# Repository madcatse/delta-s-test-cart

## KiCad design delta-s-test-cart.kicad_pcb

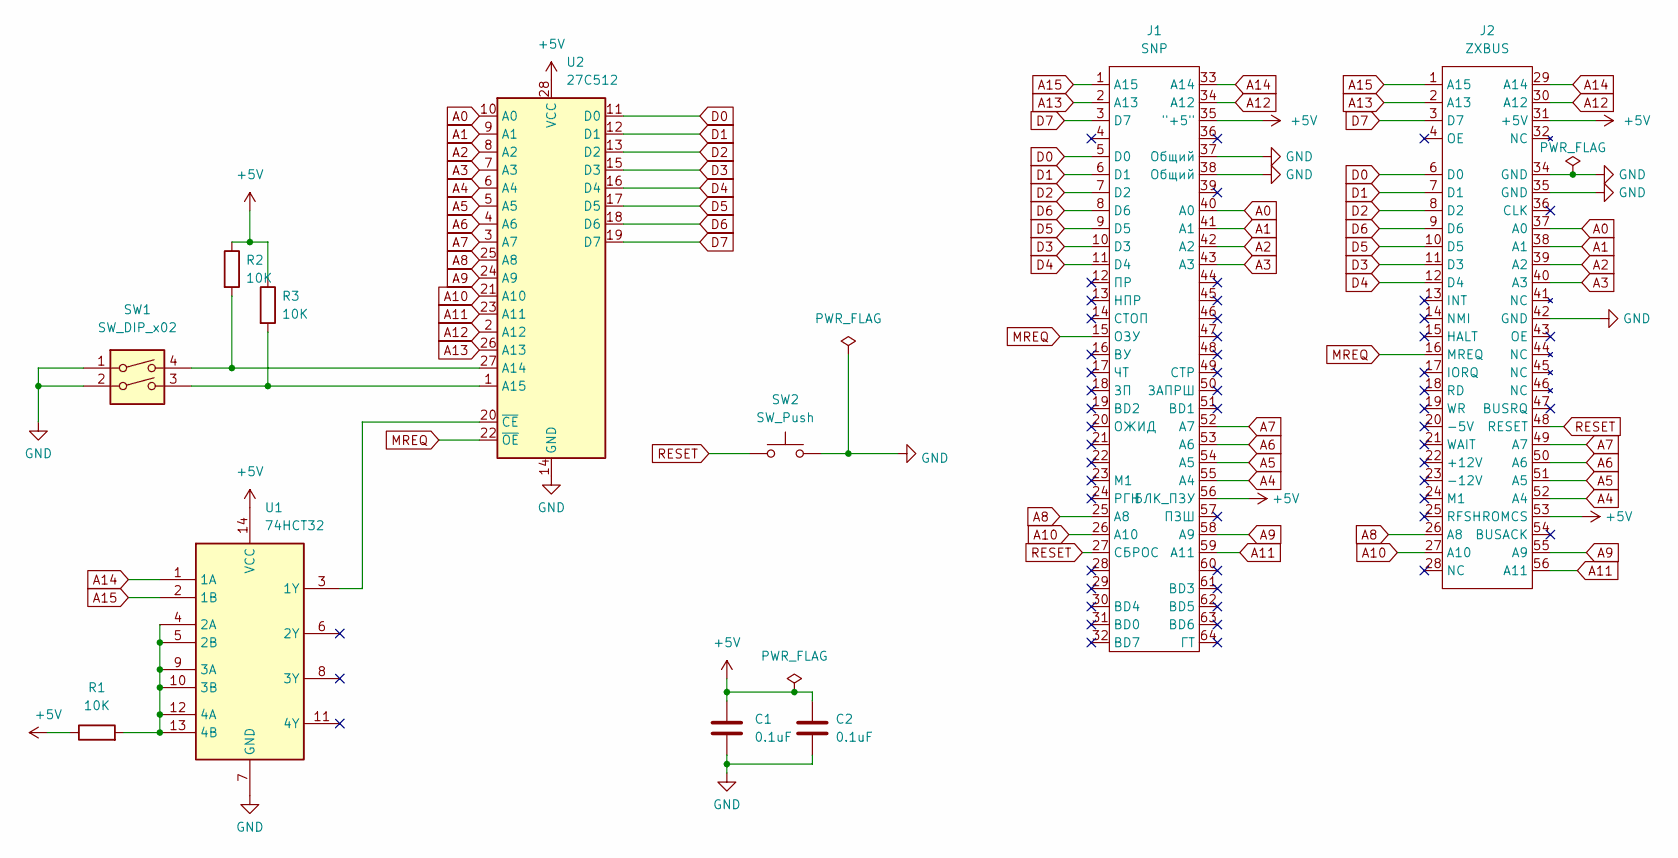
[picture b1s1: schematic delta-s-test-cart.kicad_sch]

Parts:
C1, C2: 0.1uF; C_Disc_D4.7mm_W2.5mm_P5.00mm
J1: SNP; SNP96
J2: ZXBUS; ZX SPECTRUM EDGE CONNECTOR (HORIZONTAL)
R1, R2, R3: 10K; R_Axial_DIN0207_L6.3mm_D2.5mm_P10.16mm_Horizontal
SW1: SW_DIP_x02; SW_DIP_SPSTx02_Slide_6.7x6.64mm_W7.62mm_P2.54mm_LowProfile
SW2: SW_Push; SW_PUSH_6mm
U1: 74HCT32; DIP-14_W7.62mm
U2: 27C512; DIP_Socket-28_W11.9_W12.7_W15.24_W17.78_W18.5_3M_228-1277-0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

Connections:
+5V: C1.1, C2.1, J1.35 ("+5"), J1.56 (БЛК_ПЗУ), J2.31 (+5V), J2.53 (ROMCS), R1.1, R2.1, R3.1, U1.14 (VCC), U2.28 (VCC)
A0: J1.40 (A0), J2.37 (A0), U2.10 (A0)
A1: J1.41 (A1), J2.38 (A1), U2.9 (A1)
A2: J1.42 (A2), J2.39 (A2), U2.8 (A2)
A3: J1.43 (A3), J2.40 (A3), U2.7 (A3)
A4: J1.55 (A4), J2.52 (A4), U2.6 (A4)
A5: J1.54 (A5), J2.51 (A5), U2.5 (A5)
A6: J1.53 (A6), J2.50 (A6), U2.4 (A6)
A7: J1.52 (A7), J2.49 (A7), U2.3 (A7)
A8: J1.25 (A8), J2.26 (A8), U2.25 (A8)
A9: J1.58 (A9), J2.55 (A9), U2.24 (A9)
A10: J1.26 (A10), J2.27 (A10), U2.21 (A10)
A11: J1.59 (A11), J2.56 (A11), U2.23 (A11)
A12: J1.34 (A12), J2.30 (A12), U2.2 (A12)
A13: J1.2 (A13), J2.2 (A13), U2.26 (A13)
A14: J1.33 (A14), J2.29 (A14), U1.1 (1A)
A15: J1.1 (A15), J2.1 (A15), U1.2 (1B)
D0: J1.5 (D0), J2.6 (D0), U2.11 (D0)
D1: J1.6 (D1), J2.7 (D1), U2.12 (D1)
D2: J1.7 (D2), J2.8 (D2), U2.13 (D2)
D3: J1.10 (D3), J2.11 (D3), U2.15 (D3)
D4: J1.11 (D4), J2.12 (D4), U2.16 (D4)
D5: J1.9 (D5), J2.10 (D5), U2.17 (D5)
D6: J1.8 (D6), J2.9 (D6), U2.18 (D6)
D7: J1.3 (D7), J2.3 (D7), U2.19 (D7)
GND: C1.2, C2.2, J1.37 (Общий), J1.38 (Общий), J2.34 (GND), J2.35 (GND), J2.42 (GND), SW1.1, SW1.2, SW2.2, U1.7 (GND), U2.14 (GND)
MREQ: J1.15 (ОЗУ), J2.16 (MREQ), U2.22 (~OE)
unnamed: U1.3 (1Y), U2.20 (~CE)
unnamed: R1.2, U1.4 (2A), U1.5 (2B), U1.9 (3A), U1.10 (3B), U1.12 (4A), U1.13 (4B)
unnamed: R2.2, SW1.4, U2.27 (A14)
unnamed: R3.2, SW1.3, U2.1 (A15)
RESET: J1.27 (СБРОС), J2.48 (RESET), SW2.1

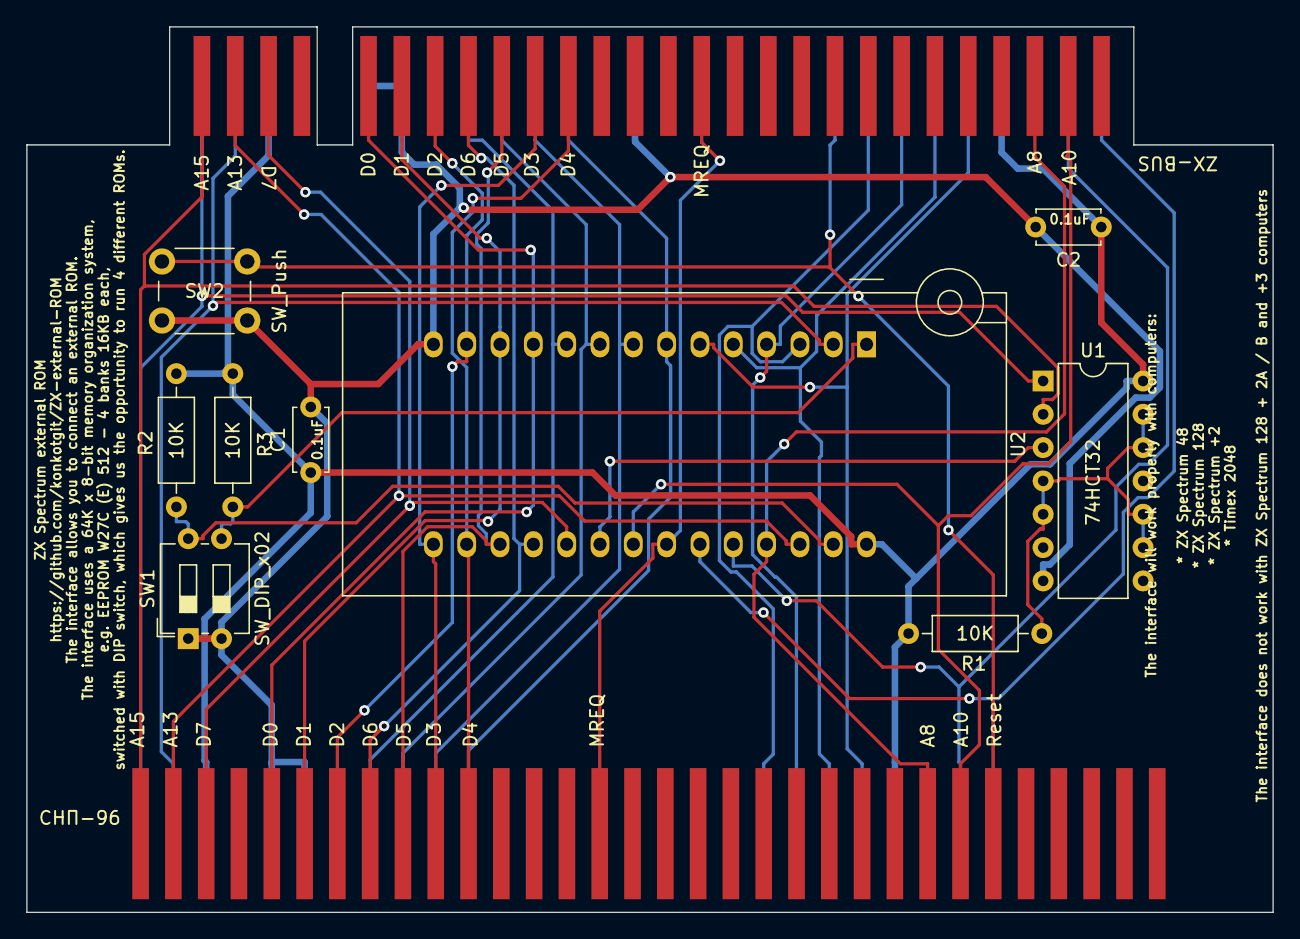
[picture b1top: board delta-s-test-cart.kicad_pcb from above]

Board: 2 copper layers, 95.0 x 67.5 mm, 11 parts (0 on the bottom side), 32 nets.

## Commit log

2023-09-09 Inital 0.1 version
2023-11-13 ROMs for cart
2024-02-06 Fixing stuff
2024-02-26 Roms
2026-05-26 26.05.2026 Update
